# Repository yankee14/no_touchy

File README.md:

# no_touchy
Project files for No Touchy, yet another bed leveling probe system

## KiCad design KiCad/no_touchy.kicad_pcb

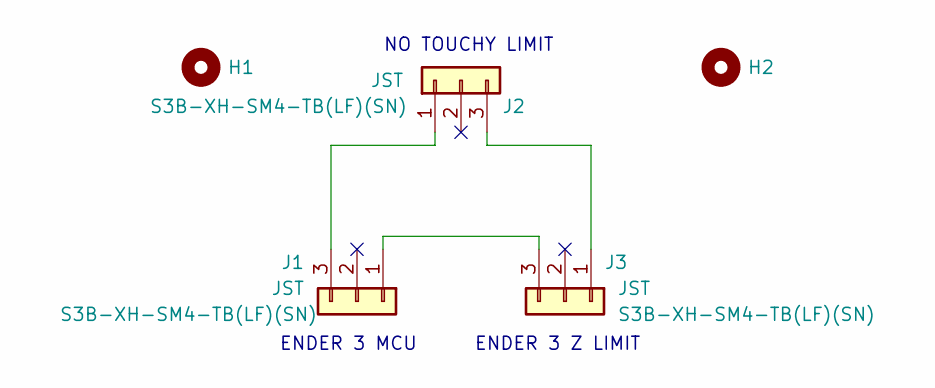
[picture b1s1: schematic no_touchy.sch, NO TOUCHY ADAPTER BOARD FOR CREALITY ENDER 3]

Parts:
H1, H2: MountingHole; MountingHole_4.3mm_M4
J1, J2, J3: Conn_01x03; JST_XH_S3B-XH-SM4_1x03_P2.50mm_Horizontal; Flammability Rating UL94 V-0; Max Voltage 250V; MPN 1 S3B-XH-SM4-TB(LF)(SN)

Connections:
unnamed: J1.1, J3.3
unnamed: J1.3, J2.1
unnamed: J2.3, J3.1

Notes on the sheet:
ENDER 3 MCU
ENDER 3 Z LIMIT
NO TOUCHY LIMIT

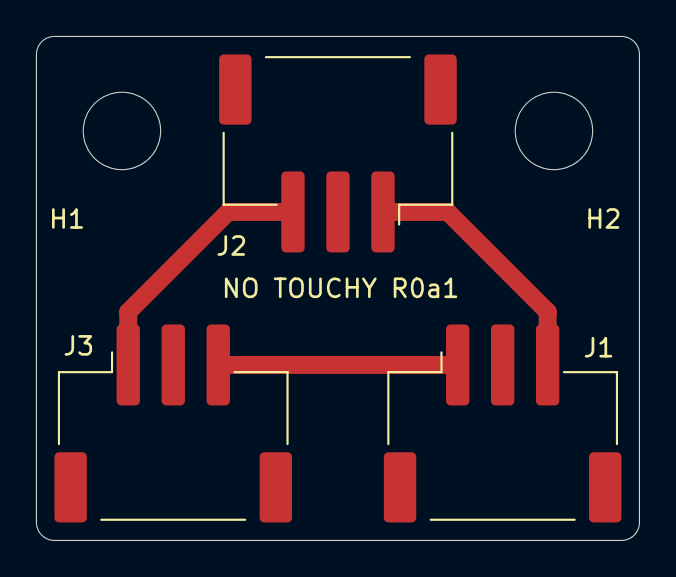
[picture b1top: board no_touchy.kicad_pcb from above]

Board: 2 copper layers, 33.5 x 28.0 mm, 5 parts (0 on the bottom side), 3 nets.

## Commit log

2020-08-24 Finish v1
2020-08-30 Refactor project file structure
2020-08-30 Add Apache 2.0 license
2020-08-30 Append KiCad gitignore entries
2020-08-30 Add GitHub README
2020-08-31 Add KiCad project
